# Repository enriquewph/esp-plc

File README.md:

# esp-plc
Proyecto de "Maquinas e Instalaciones Eléctricas": Diseño de un PLC utilizando un microcontrolador

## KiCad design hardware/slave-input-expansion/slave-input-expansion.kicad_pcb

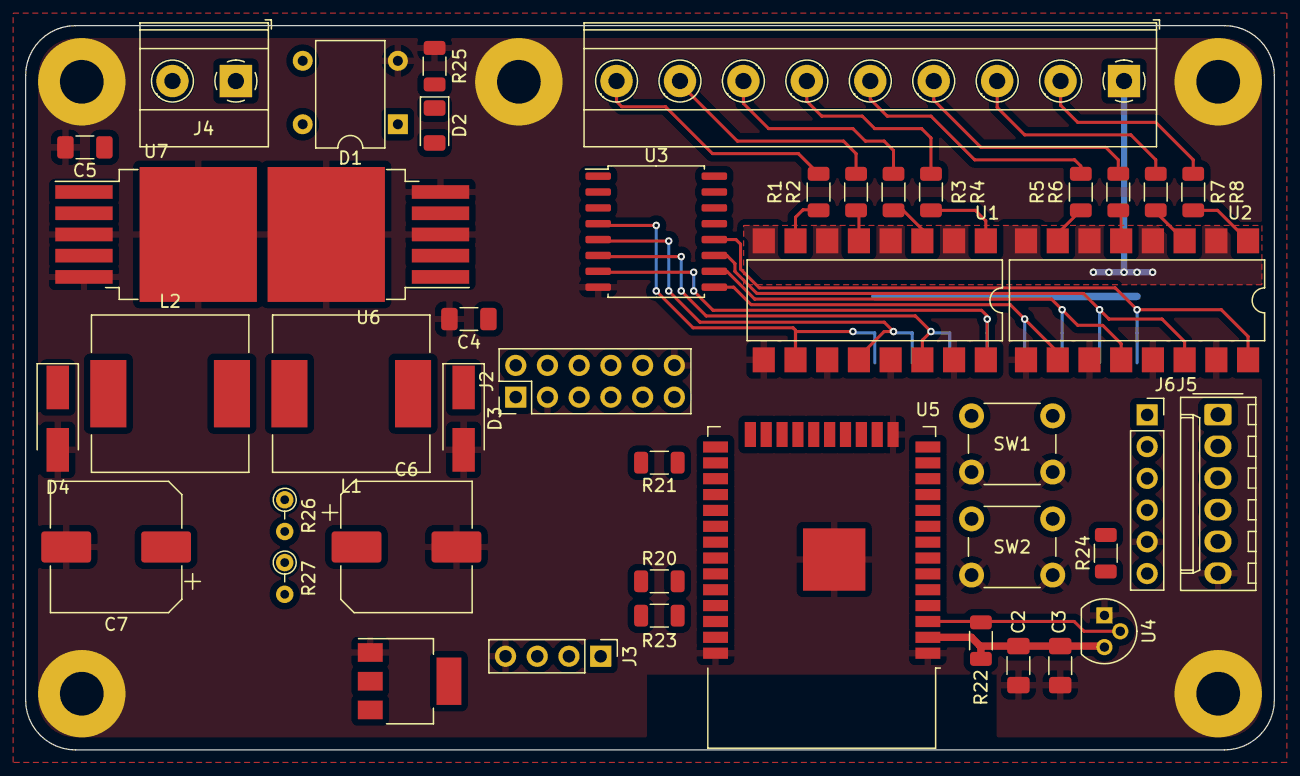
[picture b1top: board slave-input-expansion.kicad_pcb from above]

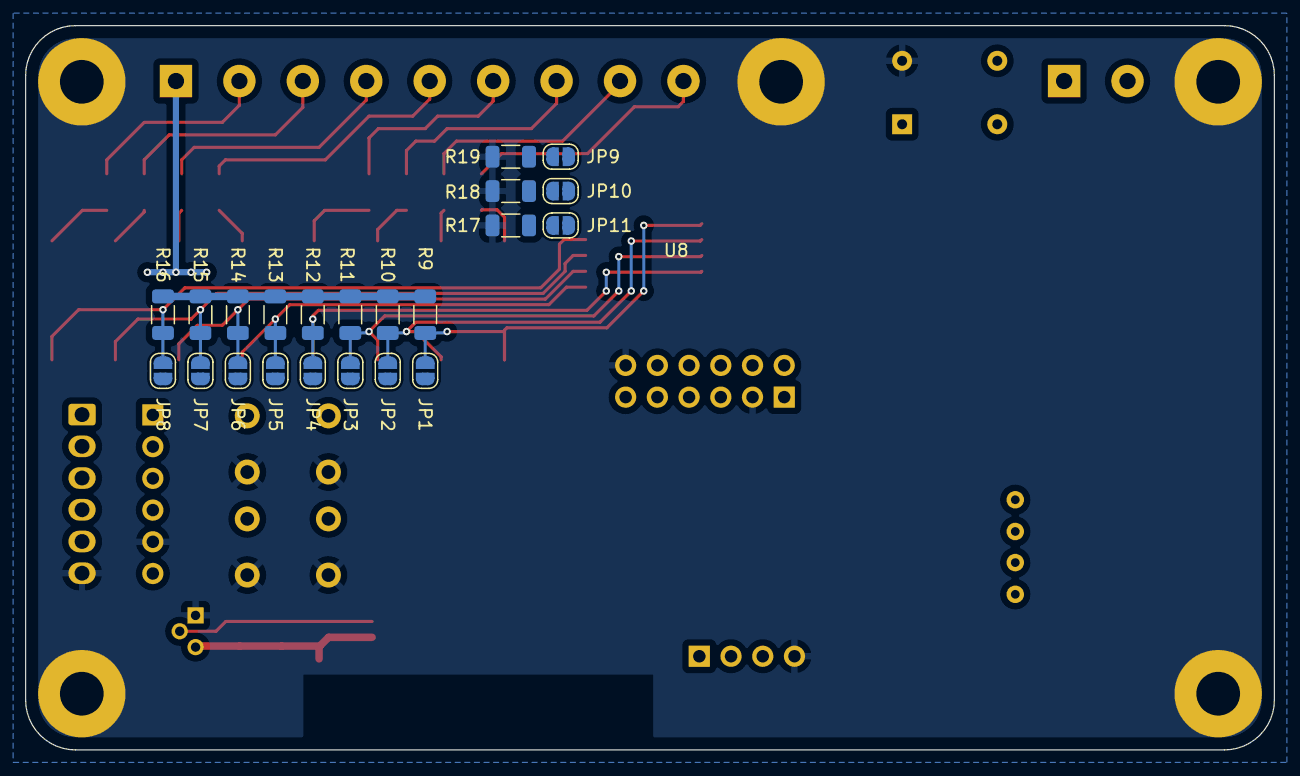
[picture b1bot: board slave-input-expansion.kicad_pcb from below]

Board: 2 copper layers, 100.0 x 58.0 mm, 66 parts (22 on the bottom side), 63 nets.

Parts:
C2, C4, C5: 100nF; C_1206_3216Metric_Pad1.33x1.80mm_HandSolder
C3: 1uF; C_1206_3216Metric_Pad1.33x1.80mm_HandSolder
C6, C7: 470uF; CP_Elec_10x10
D1: DB157; Diode_Bridge_DIP-4_W7.62mm_P5.08mm
D2: LED; LED_1206_3216Metric
D3, D4: SS14; D_SMA_Handsoldering
J1: Screw_Terminal_01x09; TerminalBlock_Phoenix_MKDS-1,5-9-5.08_1x09_P5.08mm_Horizont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
J2: Conn_02x06_Odd_Even; PinHeader_2x06_P2.54mm_Vertical
J3: Conn_01x04; PinHeader_1x04_P2.54mm_Vertical
J4: Screw_Terminal_01x02; TerminalBlock_Phoenix_MKDS-1,5-2-5.08_1x02_P5.08mm_Horizont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
J5: Conn_01x06; Molex_KK-254_AE-6410-06A_1x06_P2.54mm_Vertical
J6: ICSP; PinSocket_1x06_P2.54mm_Vertical
JP1, JP2, JP3, JP4, JP5, JP6, JP7, JP8, JP9, JP10, JP11: SolderJumper_2_Open; SolderJumper-2_P1.3mm_Open_RoundedPad1.0x1.5mm
L1, L2: 68uH; L_12x12mm_H8mm
R1, R2, R3, R4, R5, R6, R7, R8: 1k; R_1206_3216Metric
R9, R10, R11, R12, R13, R14, R15, R16, R17, R18, R19, R20, R21, R22, R23, R24: 10k; R_1206_3216Metric
R25: 4K7; R_1206_3216Metric
R26: 5.6K; R_Axial_DIN0204_L3.6mm_D1.6mm_P2.54mm_Vertical
R27: 12K; R_Axial_DIN0204_L3.6mm_D1.6mm_P2.54mm_Vertical
SW1, SW2: SW_Push; SW_PUSH_6mm
U1, U2: LTV-847S; SMDIP-16_W9.53mm
U3: PCF8574; SOIC-16W_7.5x10.3mm_P1.27mm
U4: DS1233A-10; TO-92
U5: ESP32; ESP32-WROOM-32
U6, U7: LM2596S-3.3; TO-263-5_TabPin3
U8: AMS1117-5.0; SOT-223-3_TabPin2

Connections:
+3V3: C2.1, C3.1, C7.1, J2.2, J5.4, J6.6, JP9.1 (A), JP10.1 (A), JP11.1 (A), L2.2, R9.1, R10.1, R11.1, R12.1, R13.1, R14.1, R15.1, R16.1, R20.1, R21.2, R22.1, R23.1, R24.1, U3.16 (VDD), U4.3 (VDD), U5.2 (VDD), U7.4 (FB)
+5V: J3.3, J5.5, U8.2 (VO)
+12V: C6.1, J2.1, L1.2, R27.2, U8.3 (VI)
/Power Supply/VIN: C4.1, C5.1, D1.1 (+), D2.2 (A), U6.1 (VIN), U7.1 (VIN)
ESP_IN0: JP1.2 (B), U5.13 (IO14)
ESP_IN1: JP2.2 (B), U5.16 (IO13)
ESP_IN2: JP3.2 (B), U5.8 (IO32)
ESP_IN3: JP4.2 (B), U5.9 (IO33)
ESP_IN4: JP5.2 (B), U5.6 (IO34)
ESP_IN5: JP6.2 (B), U5.7 (IO35)
ESP_IN6: JP7.2 (B), U5.4 (SENSOR_VP)
ESP_IN7: JP8.2 (B), U5.5 (SENSOR_VN)
GND: C2.2, C3.2, C4.2, C5.2, C6.2, C7.2, D1.2 (-), D3.2 (A), D4.2 (A), J2.3, J2.12, J3.4, J5.6, J6.5, R17.2, R18.2, R19.2, R25.2, SW1.1, SW2.1, U1.9, U1.11, U1.13, U1.15, U2.9, U2.11, U2.13, U2.15, U3.8 (VSS), U4.1 (GND), U5.1 (GND), U5.15 (GND), U5.38 (GND), U5.39 (GND), U6.3 (GND), U6.5 (~ON/OFF), U7.3 (GND), U7.5 (~ON/OFF), U8.1 (GND)
GPIO0: J6.4, R24.2, SW2.2, U5.25 (IO0)
IN0: JP1.1 (A), R9.2, U1.10, U3.4 (P0)
IN1: JP2.1 (A), R10.2, U1.12, U3.5 (P1)
IN2: JP3.1 (A), R11.2, U1.14, U3.6 (P2)
IN3: JP4.1 (A), R12.2, U1.16, U3.7 (P3)
IN4: JP5.1 (A), R13.2, U2.10, U3.9 (P4)
IN5: JP6.1 (A), R14.2, U2.12, U3.10 (P5)
IN6: JP7.1 (A), R15.2, U2.14, U3.11 (P6)
IN7: JP8.1 (A), R16.2, U2.16, U3.12 (P7)
INT: J5.1, R21.1, U3.13 (~INT), U5.26 (IO4)
unnamed: D1.3, J4.1
unnamed: D1.4, J4.2
unnamed: D2.1 (K), R25.1
unnamed: D3.1 (K), L1.1, U6.2 (OUT)
unnamed: D4.1 (K), L2.1, U7.2 (OUT)
unnamed: J1.1, U1.2, U1.4, U1.6, U1.8, U2.2, U2.4, U2.6, U2.8
unnamed: J1.2, R8.1
unnamed: J1.3, R7.1
unnamed: J1.4, R6.1
unnamed: J1.5, R5.1
unnamed: J1.6, R4.1
unnamed: J1.7, R3.1
unnamed: J1.8, R2.1
unnamed: J1.9, R1.1
unnamed: JP9.2 (B), R19.1, U3.1 (A0)
unnamed: JP10.2 (B), R18.1, U3.2 (A1)
unnamed: JP11.2 (B), R17.1, U3.3 (A2)
unnamed: R1.2, U1.7
unnamed: R2.2, U1.5
unnamed: R3.2, U1.3
unnamed: R4.2, U1.1
unnamed: R5.2, U2.7
unnamed: R6.2, U2.5
unnamed: R7.2, U2.3
unnamed: R8.2, U2.1
unnamed: R26.1, U6.4 (FB)
unnamed: R26.2, R27.1
OUT0: J2.4, U5.37 (IO23)
OUT1: J2.5, U5.10 (IO25)
OUT2: J2.6, U5.11 (IO26)
OUT3: J2.7, U5.12 (IO27)
OUT4: J2.8, U5.27 (IO16)
OUT5: J2.9, U5.28 (IO17)
OUT6: J2.10, U5.30 (IO18)
OUT7: J2.11, U5.31 (IO19)
RESET: J6.1, R22.2, SW1.2, U4.2 (~RESET), U5.3 (EN)
RXD0: J6.3, U5.34 (RXD0/IO3)
SCL: J3.1, J5.2, R23.2, U3.14 (SCL), U5.36 (IO22)
SDA: J3.2, J5.3, R20.2, U3.15 (SDA), U5.33 (IO21)
TXD0: J6.2, U5.35 (TXD0/IO1)

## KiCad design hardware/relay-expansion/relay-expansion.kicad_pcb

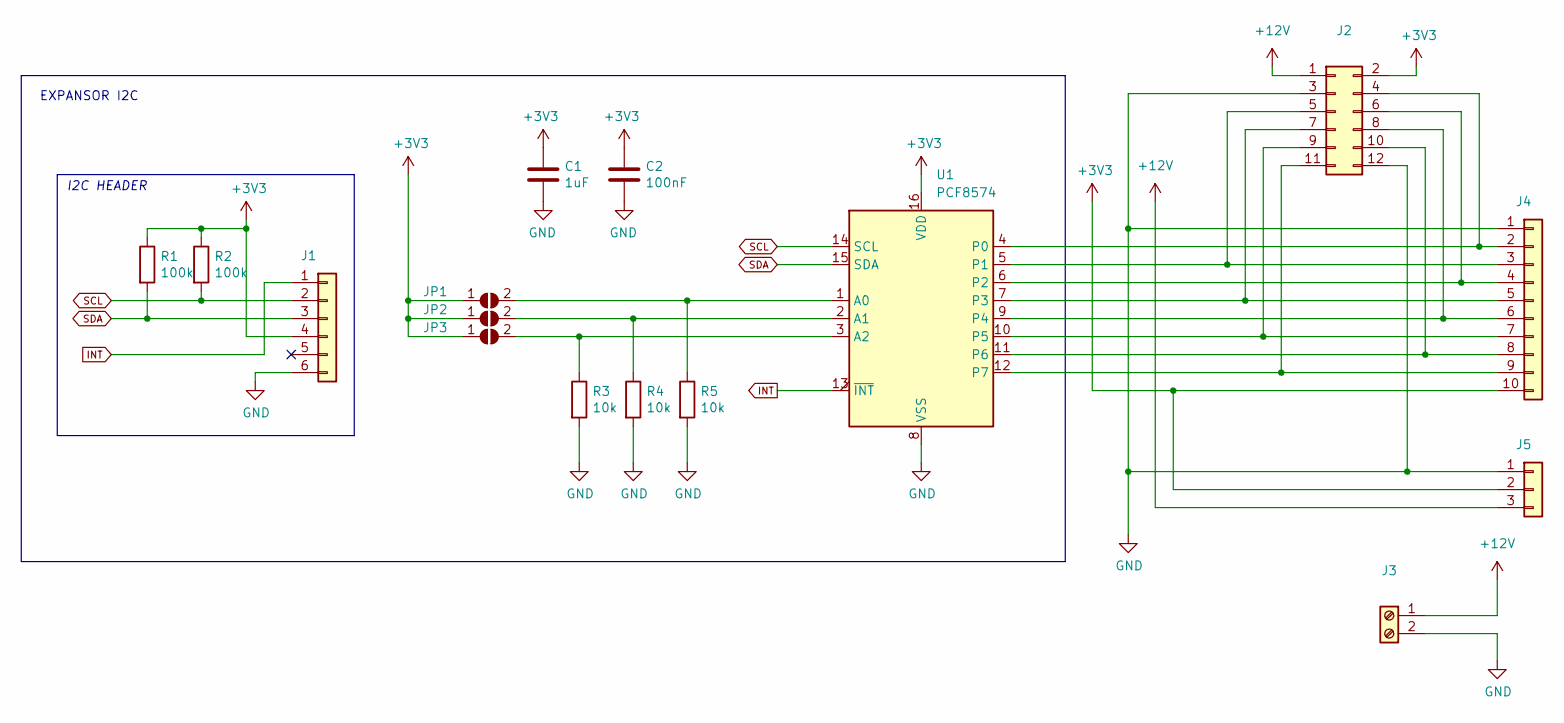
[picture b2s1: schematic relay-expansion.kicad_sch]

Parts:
C1: 1uF; C_1206_3216Metric_Pad1.33x1.80mm_HandSolder; Voltage 50V
C2: 100nF; C_1206_3216Metric_Pad1.33x1.80mm_HandSolder; Voltage 50V
J1: Conn_01x06; Molex_KK-254_AE-6410-06A_1x06_P2.54mm_Vertical
J2: Conn_02x06_Odd_Even; PinHeader_2x06_P2.54mm_Vertical
J3: (no value)
J4: Conn_01x10; PinSocket_1x10_P2.54mm_Vertical
J5: Conn_01x03; PinSocket_1x03_P2.54mm_Vertical
JP1, JP2, JP3: SolderJumper_2_Open; SolderJumper-2_P1.3mm_Open_RoundedPad1.0x1.5mm
R1, R2: 100k; R_1206_3216Metric
R3, R4, R5: 10k; R_1206_3216Metric
U1: PCF8574; SOIC-16W_7.5x10.3mm_P1.27mm

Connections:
+3V3: C1.1, C2.1, J1.4, J2.2, J4.10, J5.2, JP1.1 (A), JP2.1 (A), JP3.1 (A), R1.1, R2.1, U1.16 (VDD)
+12V: J2.1, J3.1, J5.3
GND: C1.2, C2.2, J1.6, J2.3, J2.12, J3.2, J4.1, J5.1, R3.2, R4.2, R5.2, U1.8 (VSS)
INT: J1.1, U1.13 (~INT)
unnamed: J2.4, J4.2, U1.4 (P0)
unnamed: J2.5, J4.3, U1.5 (P1)
unnamed: J2.6, J4.4, U1.6 (P2)
unnamed: J2.7, J4.5, U1.7 (P3)
unnamed: J2.8, J4.6, U1.9 (P4)
unnamed: J2.9, J4.7, U1.10 (P5)
unnamed: J2.10, J4.8, U1.11 (P6)
unnamed: J2.11, J4.9, U1.12 (P7)
unnamed: JP1.2 (B), R5.1, U1.1 (A0)
unnamed: JP2.2 (B), R4.1, U1.2 (A1)
unnamed: JP3.2 (B), R3.1, U1.3 (A2)
SCL: J1.2, R2.2, U1.14 (SCL)
SDA: J1.3, R1.2, U1.15 (SDA)

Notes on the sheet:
EXPANSOR I2C
I2C HEADER

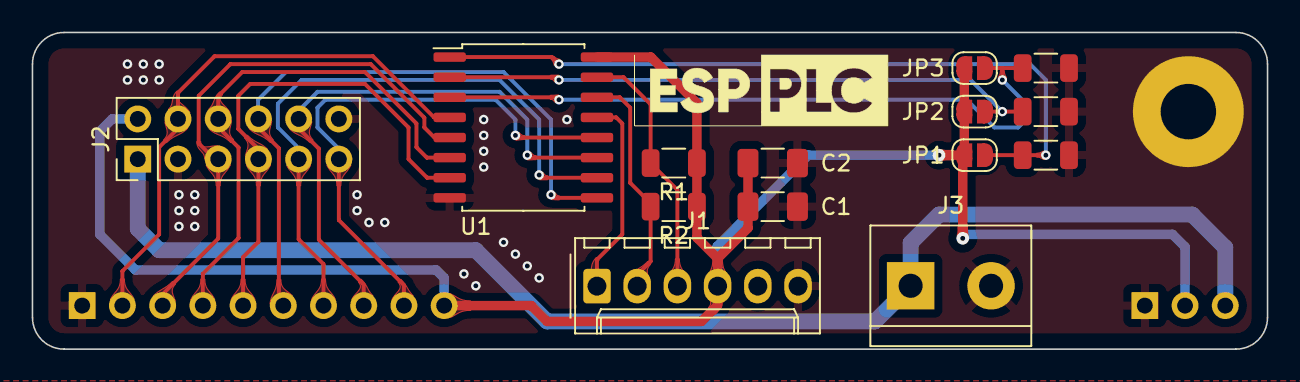
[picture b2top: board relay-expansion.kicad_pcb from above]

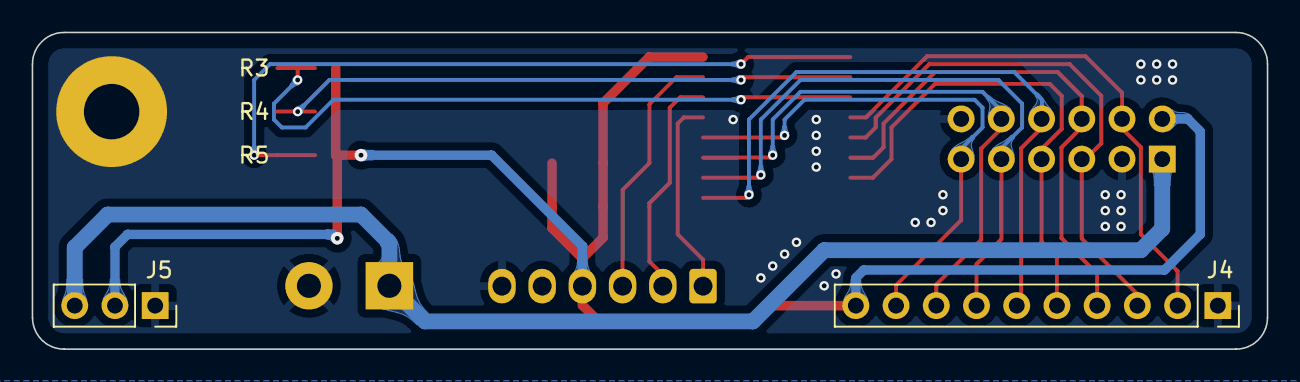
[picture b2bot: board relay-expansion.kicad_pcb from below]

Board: 2 copper layers, 78.0 x 20.0 mm, 16 parts (2 on the bottom side), 17 nets.

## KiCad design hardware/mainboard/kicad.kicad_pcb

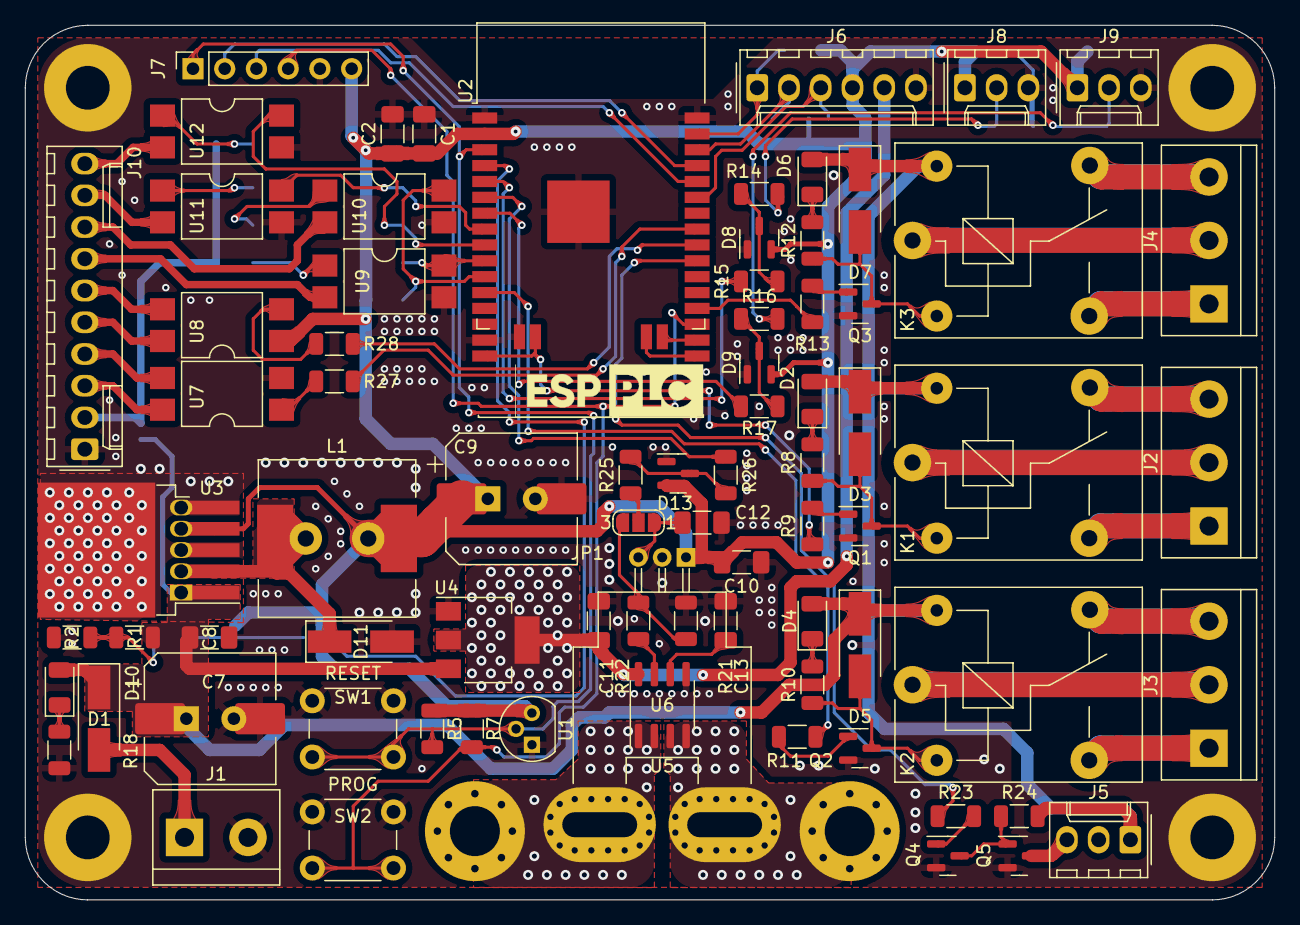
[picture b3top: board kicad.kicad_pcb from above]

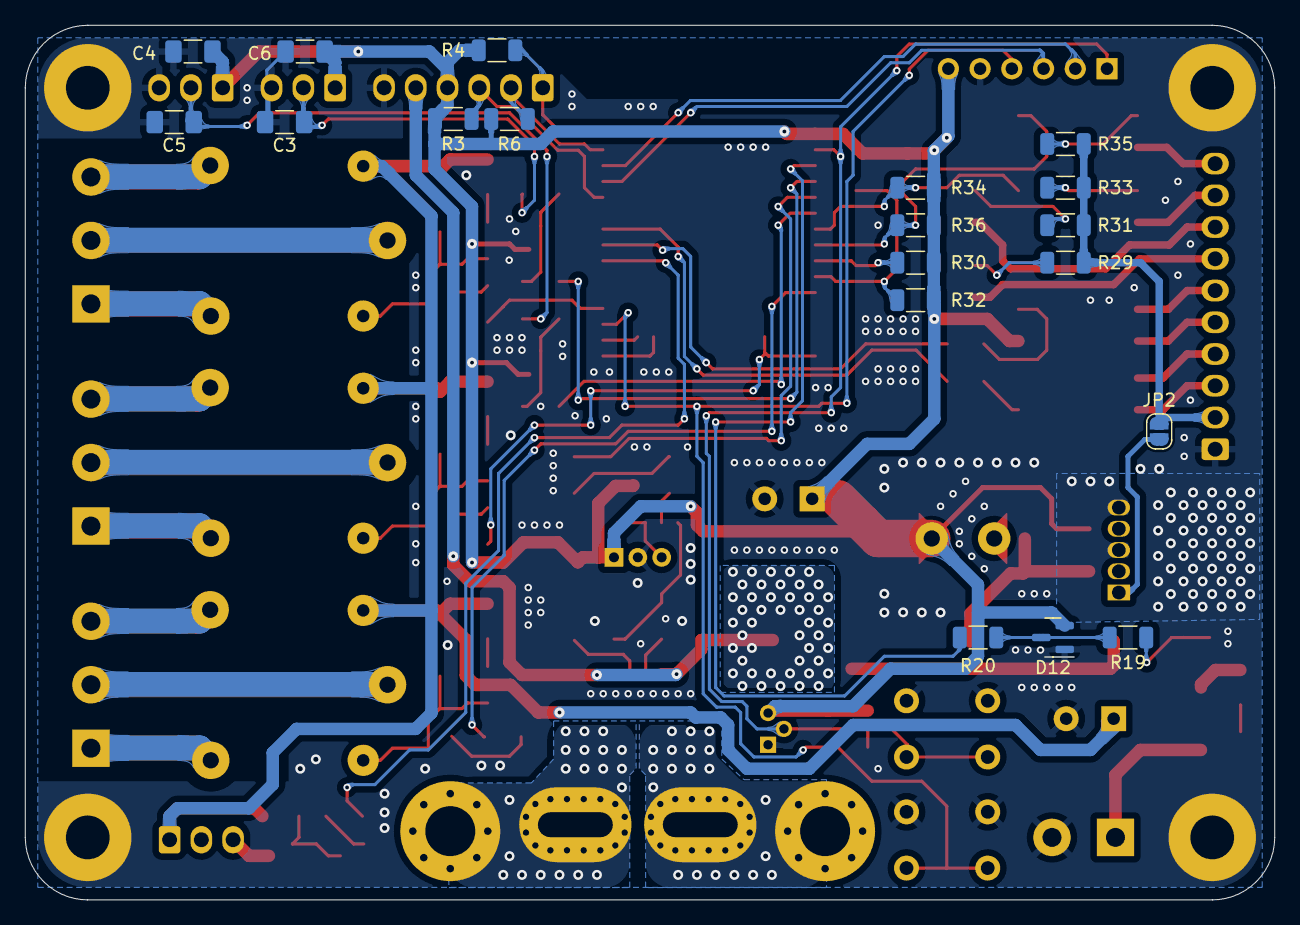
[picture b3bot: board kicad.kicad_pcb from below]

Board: 2 copper layers, 100.0 x 70.0 mm, 99 parts (19 on the bottom side), 78 nets.

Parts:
C1, C3, C4, C5, C6, C8, C10, C11, C12: 100nF; C_1206_3216Metric_Pad1.33x1.80mm_HandSolder
C2: 1uF; C_1206_3216Metric_Pad1.33x1.80mm_HandSolder
C7, C9: 470uF; CAP_10x10_SMD_THT
C13: 1nF; C_1206_3216Metric_Pad1.33x1.80mm_HandSolder
D1, D11: SS14; D_SMA_Handsoldering
D2, D4, D6, D10: LED; LED_1206_3216Metric
D3, D5, D7: M7; D_SMA_Handsoldering
D8, D9, D12, D13: BAT54S; SOT-23
H1, H2: MountingHole_Pad; MountingHole_4mm_Pad_Via
J1: Screw_Terminal_01x02; TerminalBlock_bornier-2_P5.08mm
J2, J3, J4: Screw_Terminal_01x03; TerminalBlock_bornier-3_P5.08mm
J5, J8, J9: Conn_01x03; Molex_KK-254_AE-6410-03A_1x03_P2.54mm_Vertical
J6: Conn_01x06; Molex_KK-254_AE-6410-06A_1x06_P2.54mm_Vertical
J7: ICSP; PinSocket_1x06_P2.54mm_Vertical
J10: Conn_01x10; Molex_KK-254_AE-6410-10A_1x10_P2.54mm_Vertical
JP1: SolderJumper_3_Bridged12; SolderJumper-3_P1.3mm_Open_RoundedPad1.0x1.5mm_NumberLabels
JP2: SolderJumper_2_Open; SolderJumper-2_P1.3mm_Open_RoundedPad1.0x1.5mm
K1, K2, K3: RELAY; Relay_SPDT_SANYOU_SRD_Series_Form_C
L1: 68uH; L_12x12mm_H8mm
Q1, Q2, Q3, Q4: BC817; SOT-23
Q5: IRLML2502; SOT-23
R1: 22k; R_1206_3216Metric
R2: 5k6; R_1206_3216Metric
R3, R4, R5, R6, R7, R24, R30, R32, R34, R36: 10k; R_1206_3216Metric
R8, R9, R10, R11, R12, R13, R14, R15, R16, R17, R18, R19, R20, R22, R23, R25, R26, R29, R31, R33, R35: 1k; R_1206_3216Metric
R21: 2k; R_1206_3216Metric
R27, R28: 100; R_1206_3216Metric
SW1, SW2: SW_Push; SW_PUSH_6mm
U1: DS1233A-10; TO-92
U2: ESP32; ESP32-WROOM-WROVER-NC
U3: LM2596S-3.3; TO-263-5_TabPin3
U4: AMS1117-5.0; SOT-223-3_TabPin2
U5: ACS759; Allegro_CB_PFF
U6: ACS712; SOIC-8_3.9x4.9mm_P1.27mm
U7, U8, U9, U10, U11, U12: PC817XI; SMDIP-4_W9.53mm

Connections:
+3V3: C1.1, C2.1, C4.1, C6.1, C9.1, C10.1, D8.2, D9.2, D12.2, D13.2, J6.4, J7.6, J8.1, J9.1, L1.2, R3.1, R4.2, R5.1, R6.1, R7.1, R30.1, R32.1, R34.1, R36.1, U1.3 (VDD), U2.2 (VDD), U3.4 (FB), U5.1 (VCC), U8.1
+5V: C11.1, J6.5, U4.2 (VO), U6.8 (VCC)
+12V: C7.1, C8.1, D1.1 (K), D2.2 (A), D3.1 (K), D4.2 (A), D5.1 (K), D6.2 (A), D7.1 (K), D10.2 (A), J5.1, JP2.2 (B), K1.5, K2.5, K3.5, R1.1, R24.1, U3.1 (VIN), U4.3 (VI)
+BATT: D1.2 (A), J1.1
/Current Sensor/IP+: H1.1, U5.4 (IP+), U6.1 (IP+), U6.2 (IP+)
/Current Sensor/IP-: H2.1, U5.5 (IP-), U6.3 (IP-), U6.4 (IP-)
/Current Sensor/OUT: JP1.2 (C), R25.2
/Input Protection/IN: R1.2, R2.1, R19.2
/LM35: T1/OUT: C3.1, J8.2, R14.2
/LM35: T2/OUT: C5.1, J9.2, R16.2
/Opto I/O/input-0/A: J10.2, JP2.1 (A), R29.2, R31.2, R33.2, R35.2
/Opto I/O/input-0/K: J10.7, U9.2
/Opto I/O/input-1/K: J10.8, U10.2
/Opto I/O/input-2/K: J10.9, U11.2
/Opto I/O/input-3/K: J10.10, U12.2
/Opto I/O/output-0/C: J10.5, U8.4
/Opto I/O/output-0/E: J10.6, U8.3
/Opto I/O/output-1/C: J10.3, U7.4
/Opto I/O/output-1/E: J10.4, U7.3
/Relay 1/COM: J2.2, K1.1
/Relay 1/NC: J2.3, K1.4
/Relay 1/NO: J2.1, K1.3
/Relay 2/COM: J3.2, K2.1
/Relay 2/NC: J3.3, K2.4
/Relay 2/NO: J3.1, K2.3
/Relay 3/COM: J4.2, K3.1
/Relay 3/NC: J4.3, K3.4
/Relay 3/NO: J4.1, K3.3
/Salida MOSFET/OUT: J5.3, Q5.3 (D)
FAN_1: R23.2, U2.29 (IO5)
GND: C1.2, C2.2, C3.2, C4.2, C5.2, C6.2, C7.2, C8.2, C9.2, C10.2, C11.2, C12.2, C13.2, D8.1, D9.1, D11.2 (A), D12.1, D13.1, J1.2, J6.6, J7.5, J8.3, J9.3, J10.1, Q1.2 (E), Q2.2 (E), Q3.2 (E), Q4.2 (E), Q5.2 (S), R2.2, R18.2, R21.1, SW1.1, SW2.1, U1.1 (GND), U2.1 (GND), U2.15 (GND), U2.38 (GND), U2.39 (GND), U3.3 (GND), U3.5 (~ON/OFF), U4.1 (GND), U5.2 (GND), U6.5 (GND), U7.2, U9.3, U10.3, U11.3, U12.3
GPIO0: J7.4, R7.2, SW2.2, U2.25 (IO0)
IBAT: R26.1, U2.6 (IO34)
IN0: R30.2, U2.10 (IO25), U9.4
IN1: R32.2, U2.11 (IO26), U10.4
IN2: R34.2, U2.8 (IO32), U11.4
IN3: R36.2, U2.9 (IO33), U12.4
INT: J6.1, R4.1, U2.37 (IO23)
unnamed: C12.1, JP1.1 (A), U5.3 (VIOUT)
unnamed: C13.1, U6.6 (FILTER)
unnamed: D2.1 (K), R8.1
unnamed: D3.2 (A), K1.2, Q1.3 (C), R8.2
unnamed: D4.1 (K), R10.1
unnamed: D5.2 (A), K2.2, Q2.3 (C), R10.2
unnamed: D6.1 (K), R12.1
unnamed: D7.2 (A), K3.2, Q3.3 (C), R12.2
unnamed: D8.3, R14.1, R15.2
unnamed: D9.3, R16.1, R17.2
unnamed: D10.1 (K), R18.1
unnamed: D11.1 (K), L1.1, U3.2 (OUT)
unnamed: D12.3, R19.1, R20.2
unnamed: D13.3, R25.1, R26.2
unnamed: JP1.3 (B), R21.2, R22.1
unnamed: Q1.1 (B), R9.1
unnamed: Q2.1 (B), R11.1
unnamed: Q3.1 (B), R13.1
unnamed: Q4.1 (B), R23.1
unnamed: Q4.3 (C), Q5.1 (G), R24.2
unnamed: R22.2, U6.7 (VIOUT)
unnamed: R27.1, U7.1
unnamed: R28.1, U8.2
unnamed: R29.1, U9.1
unnamed: R31.1, U10.1
unnamed: R33.1, U11.1
unnamed: R35.1, U12.1
OUT0: R28.2, U2.30 (IO18)
OUT1: R27.2, U2.31 (IO19)
RELAY_1: R9.2, U2.16 (IO13)
RELAY_2: R11.2, U2.12 (IO27)
RELAY_3: R13.2, U2.26 (IO4)
RESET: J7.1, R5.2, SW1.2, U1.2 (~RESET), U2.3 (EN)
RXD0: J7.3, U2.34 (RXD0/IO3)
SCL: J6.2, R6.2, U2.36 (IO22)
SDA: J6.3, R3.2, U2.33 (IO21)
TBAT: R15.1, U2.5 (SENSOR_VN)
TEMP2: R17.1, U2.7 (IO35)
TXD0: J7.2, U2.35 (TXD0/IO1)
VBAT: R20.1, U2.4 (SENSOR_VP)

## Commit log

2023-04-28 Eliminar backups
2023-04-28 Added assignment
2023-04-28 Move tp doc file
2023-04-28 move project files
2023-04-28 add software submodule
2023-04-28 add relay expansion pcb
2023-04-28 add standalone input slave pcb
2023-04-29 Diseños casi listos (sch)
2023-05-02 Mainboard routeado.
2023-05-03 PCB Design for relay-expansion board done, added mechanical 3d files (solidworks 2016)
2023-05-03 track lfs files
2023-05-03 convert files to LFS
2023-05-03 Diseño mecanico del ensamblaje
2023-05-04 Routeo de la placa expansion
2023-05-04 switch to 12v psu
